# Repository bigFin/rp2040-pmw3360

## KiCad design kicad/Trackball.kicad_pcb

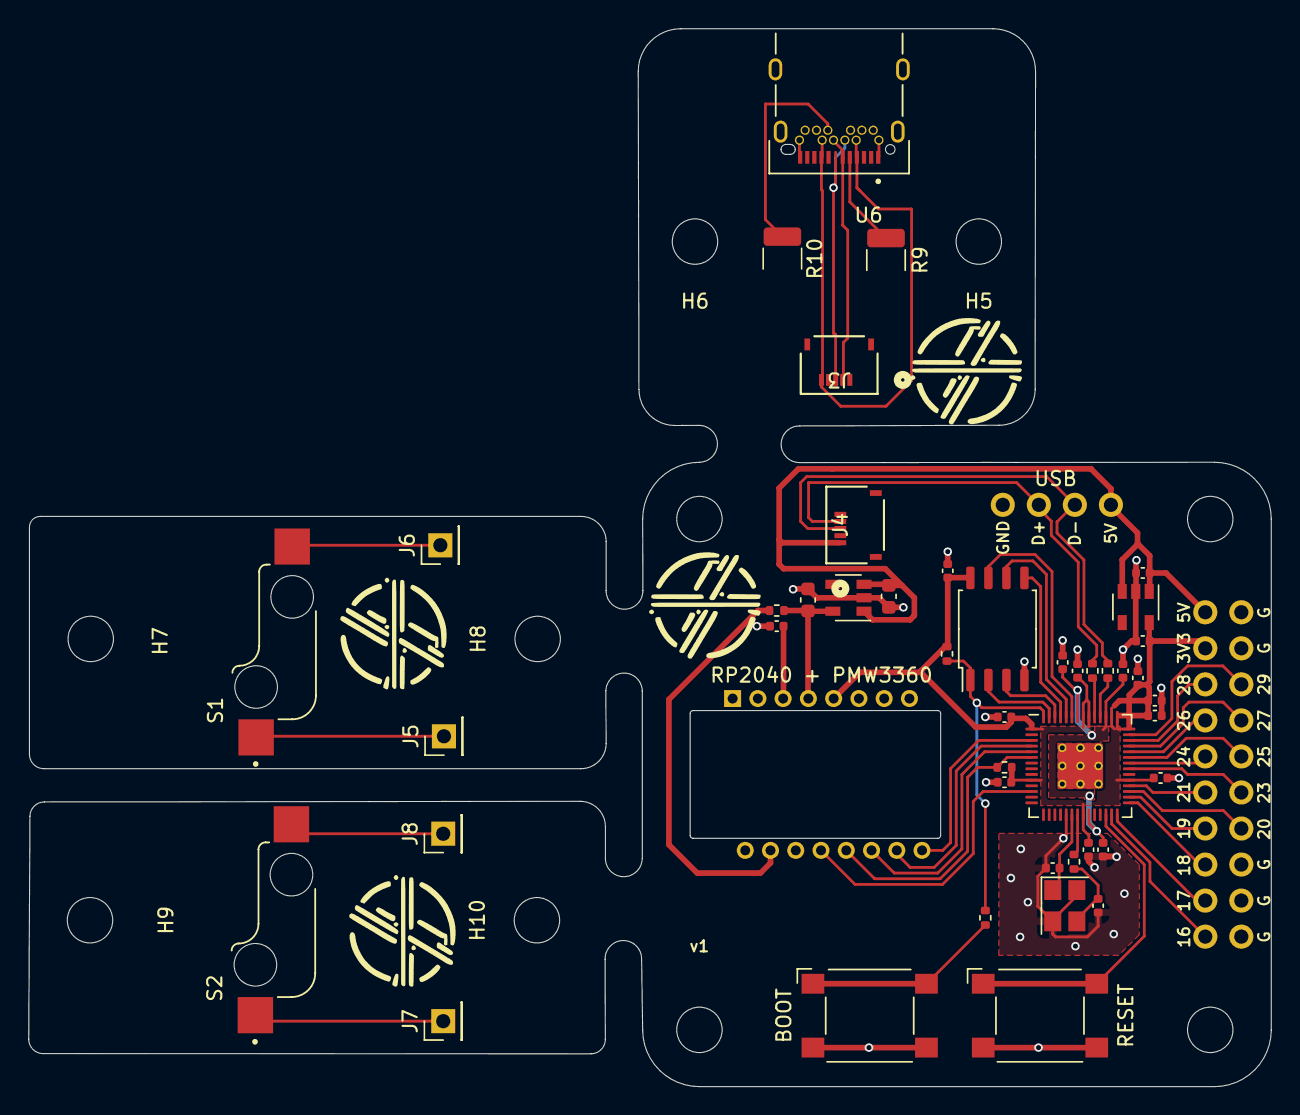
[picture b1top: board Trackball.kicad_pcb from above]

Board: 2 copper layers, 87.6 x 74.6 mm, 57 parts (1 on the bottom side), 49 nets.

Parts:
C1, C2: 30p; C_0402_1005Metric
C3, C5, C10, C16: 1u; C_0402_1005Metric
C4: 4.7u; C_0402_1005Metric
C6: 0.1u; C_0603_1608Metric
C7, C9, C11, C12, C13, C14, C15, C17, C18, C19: 100n; C_0402_1005Metric
C8: 1u; C_0603_1608Metric
H1, H2, H3, H4, H5, H6, H7, H8, H9, H10: MountingHole; MountingHole_3.2mm_M3
J1: Conn_02x10_Odd_Even; PinHeader_2x10_P2.54mm_Vertical
J2: Conn_01x04; PinHeader_1x04_P2.54mm_Vertical
J3, J4: FH34SRJ-6S-0.5SH50; CONN6x1_FH34SRJ-6S-0.5SH50_HIR
J5, J6, J7, J8: Conn_01x01; PinHeader_1x01_P2.54mm_Vertical
R1, R2: 1k; R_0402_1005Metric
R3, R5: 10k; R_0402_1005Metric
R4: 39; R_0402_1005Metric
R6, R7: 27; R_0402_1005Metric
R9, R10: 5.1k; R_1210_3225Metric_Pad1.30x2.65mm_HandSolder
S1, S2: PG151101S11; SW_PG151101S11
SW1, SW2: SW_Push; SW_SPST_Omron_B3FS-100xP
U1: TLV73333PDBV; SOT-23-5
U2: PMW3360
U3: W25Q128JVS; SOIC-8_5.23x5.23mm_P1.27mm
U4: TCR2EF19; SOT-23-5
U5: RP2040; RP2040-QFN-56
U6: TYPE-C-31-M-14; AMPHENOL_GSB3CA11310DSHR
Y1: Crystal_GND24; Crystal_SMD_3225-4Pin_3.2x2.5mm

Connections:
+: J3.6, U6.A4 (VBUS_A), U6.A9 (VBUS_A__1), U6.B4 (VBUS_B), U6.B9 (VBUS_B__1)
+1V1: C9.1, C10.1, C11.1, U5.23 (DVDD), U5.45 (VREG_VOUT), U5.50 (DVDD)
+1V8: C8.1, R4.1, U2.4 (VDD), U4.5 (OUT)
+3V3: C5.1, C7.1, C12.1, C13.1, C14.1, C15.1, C16.1, C17.1, C18.1, C19.1, J1.3, R3.1, R5.1, U1.5 (OUT), U2.5 (VDDIO), U3.8 (VCC), U5.1 (IOVDD), U5.10 (IOVDD), U5.22 (IOVDD), U5.33 (IOVDD), U5.42 (IOVDD), U5.43 (ADC_AVDD), U5.44 (VREG_IN), U5.48 (USB_VDD), U5.49 (IOVDD)
+5V: C3.1, C6.2, J1.1, J2.1, J4.1, U1.1 (IN), U1.3 (EN), U4.1 (IN), U4.3 (EN)
D+: J2.3, J4.4, R6.1
D-: J2.2, J4.3, R7.1
DN: J3.4, U6.A7 (DN1), U6.B7 (DN2)
DP: J3.3, U6.A6 (DP1), U6.B6 (DP2)
GND-USB: C1.1, C2.2, C3.2, C4.2, C5.2, C6.1, C7.2, C8.2, C9.2, C10.2, C11.2, C12.2, C13.2, C14.2, C15.2, C16.2, C17.2, C18.2, C19.2, J1.2, J1.4, J1.16, J1.18, J1.20, J2.4, J3.1, J4.6, R9.2 (-), R10.2 (-), SW1.1, SW2.1, U1.2 (GND), U2.8 (GND), U3.4 (GND), U4.2 (GND), U5.19 (TESTEN), U5.57 (GND), U6.A1 (GND_A), U6.A12 (GND_A__1), U6.B1 (GND_B), U6.B12 (GND_B__1), Y1.2, Y1.4
GPIO16: J1.19, U5.27 (GPIO16)
GPIO17: J1.17, U5.28 (GPIO17)
GPIO18: J1.15, U5.29 (GPIO18)
GPIO19: J1.13, U5.30 (GPIO19)
GPIO20: J1.14, U5.31 (GPIO20)
GPIO21: J1.11, U5.32 (GPIO21)
GPIO23: J1.12, U5.35 (GPIO23)
GPIO24: J1.9, U5.36 (GPIO24)
GPIO25: J1.10, U5.37 (GPIO25)
GPIO26: J1.7, U5.38 (GPIO26_ADC0)
GPIO27: J1.8, U5.39 (GPIO27_ADC1)
GPIO28: J1.5, U5.40 (GPIO28_ADC2)
GPIO29: J1.6, U5.41 (GPIO29_ADC3)
MISO: R5.2, U2.12 (MISO), U5.6 (GPIO4)
MOSI: U2.11 (MOSI), U5.5 (GPIO3)
MOTION: U2.9 (MOTION), U5.3 (GPIO1)
NCS: U2.13 (NCS), U5.12 (GPIO9)
unnamed: C2.1, R1.1, Y1.3
unnamed: J5.1, S1.1
unnamed: J6.1, S1.2
unnamed: J7.1, S2.1
unnamed: J8.1, S2.2
unnamed: R2.2, SW1.2
unnamed: R9.1 (+), U6.A5 (CC1)
unnamed: R10.1 (+), U6.B5 (CC2)
unnamed: R4.2, U2.15 (LED_P)
unnamed: C4.1, U2.3 (VDDPIX)
unnamed: SW2.2, U5.26 (RUN)
unnamed: R7.2, U5.46 (USB_DM)
unnamed: R6.2, U5.47 (USB_DP)
QSPI_SCLK: U3.6 (CLK), U5.52 (QSPI_SCLK)
QSPI_SD0: U3.5 (DI(IO0)), U5.53 (QSPI_SD0)
QSPI_SD1: U3.2 (DO(IO1)), U5.55 (QSPI_SD1)
QSPI_SD2: U3.3 (IO2), U5.54 (QSPI_SD2)
QSPI_SD3: U3.7 (IO3), U5.51 (QSPI_SD3)
QSPI_SS: R2.1, R3.2, U3.1 (~CS), U5.56 (QSPI_SS)
SCLK: U2.10 (SCLK), U5.4 (GPIO2)
XIN: C1.2, U5.20 (XIN), Y1.1
XOUT: R1.2, U5.21 (XOUT)

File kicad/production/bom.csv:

Designator,Footprint,Quantity,Value,LCSC Part #
"C1, C2",0402,2,30p,C1570
"C10, C16, C3, C5",0402,4,1u,C52923
"C11, C12, C13, C14, C15, C17, C18, C19, C7, C9",0402,10,100n,C1525
C4,0402,1,4.7u,C23733
C6,0603,1,0.1u,C14663
C8,0603,1,1u,C15849
"H1, H10, H2, H3, H4, H5, H6, H7, H8, H9",MountingHole_3.2mm_M3,10,MountingHole,
J2,PinHeader_1x04_P2.54mm_Vertical,1,Conn_01x04,
"J3, J4",CONN6x1_FH34SRJ-6S-0.5SH50_HIR,2,FH34SRJ-6S-0.5SH50,
"R1, R2",0402,2,1k,C11702
"R10, R9",1210,2,5.1k,
"R3, R5",0402,2,10k,C25744
R4,0402,1,39,C25110
"R6, R7",0402,2,27,C138021
"S1, S2",SW_PG151101S11,2,PG151101S11,
"SW1, SW2",SW_SPST_Omron_B3FS-100xP,2,SW_Push,C271750
U1,SOT-23-5,1,TLV73333PDBV,C134139
U2,PMW3360,1,PMW3360,
U3,SOIC-8_5.23x5.23mm_P1.27mm,1,W25Q128JVS,C97521
U4,SOT-23-5,1,TCR2EF19,C146366
U5,RP2040-QFN-56,1,RP2040,C2040
U6,AMPHENOL_GSB3CA11310DSHR,1,TYPE-C-31-M-14,
Y1,Crystal_SMD_3225-4Pin_3.2x2.5mm,1,Crystal_GND24,C9002
